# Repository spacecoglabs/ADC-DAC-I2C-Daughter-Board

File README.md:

# ADC-DAC-I2C-Daughter-Board
A simple KiCAD design for an I2C based daughter board featuring a DAC and a ADC.

## Overview
This repository contains a simple KiCADv6 design for a I2C daughter board featuring a TI DAC5571 DAC and a TI ADC081C021 ADC. This design allows for simultaneous electrical connections to the DAC and ADC using the same reference ground utilizing the provided three pin screw terminal.

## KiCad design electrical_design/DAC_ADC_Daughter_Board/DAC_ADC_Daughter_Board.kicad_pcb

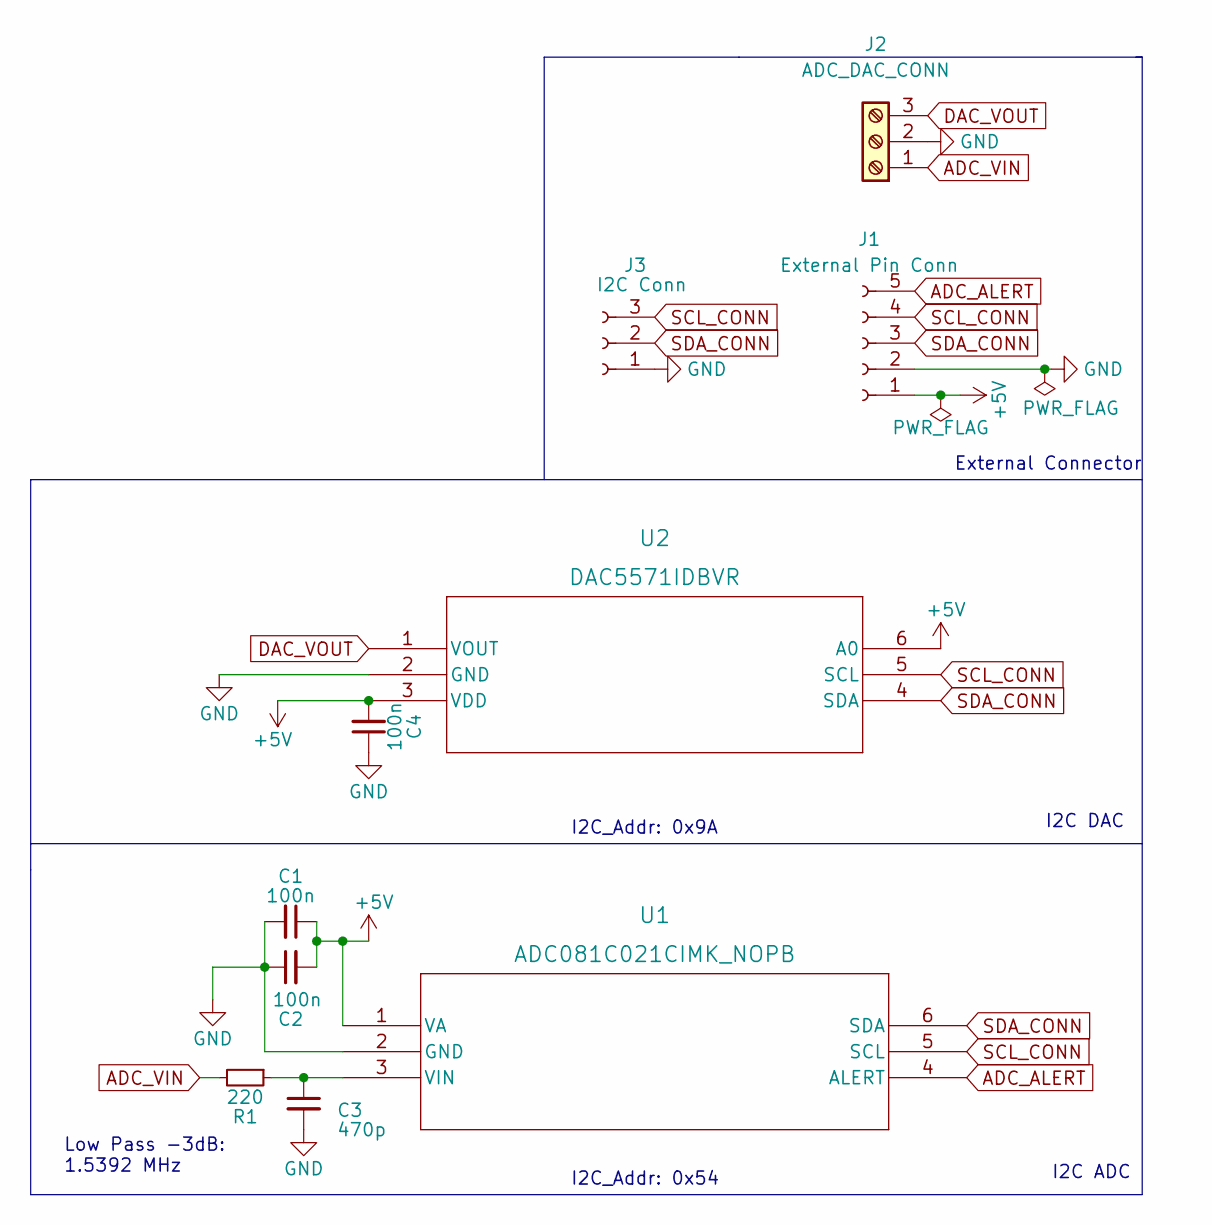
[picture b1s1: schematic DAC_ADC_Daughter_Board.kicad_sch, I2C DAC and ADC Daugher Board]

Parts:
C1, C2, C4: 100n; C_0603_1608Metric; LCSC C14663
C3: 470p; C_0603_1608Metric; LCSC C1620
J1: External Pin Conn; Conn_5
J2: ADC_DAC_CONN; ThreePinScrewTerminal
J3: I2C Conn; Conn_3
R1: 220; R_0805_2012Metric; LCSC C17557
U1: ADC081C021CIMK_NOPB; ADC081C021CIMK; LCSC C181423
U2: DAC5571IDBVR; LCSC C24061

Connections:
+5V: C1.1, C2.2, C4.2, J1.1, U1.1 (VA), U2.3 (VDD), U2.6 (A0)
ADC_ALERT: J1.5, U1.4 (ALERT)
ADC_VIN: J2.1, R1.2
DAC_VOUT: J2.3, U2.1 (VOUT)
GND: C1.2, C2.1, C3.2, C4.1, J1.2, J2.2, J3.1, U1.2 (GND), U2.2 (GND)
unnamed: C3.1, R1.1, U1.3 (VIN)
SCL_CONN: J1.4, J3.3, U1.5 (SCL), U2.5 (SCL)
SDA_CONN: J1.3, J3.2, U1.6 (SDA), U2.4 (SDA)

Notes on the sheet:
I2C DAC
I2C ADC
External Connector
I2C_Addr: 0x54
Low Pass -3dB: 1.5392 MHz
I2C_Addr: 0x9A

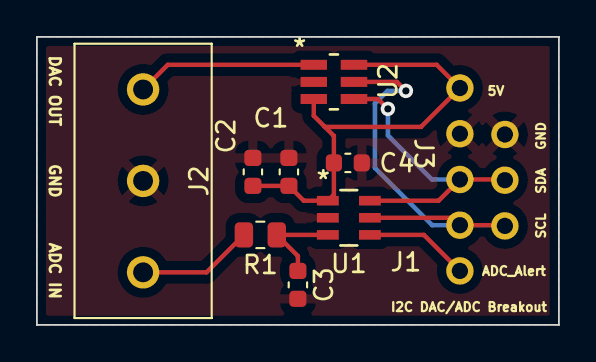
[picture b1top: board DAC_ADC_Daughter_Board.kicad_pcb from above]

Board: 2 copper layers, 29.0 x 16.0 mm, 10 parts (0 on the bottom side), 8 nets.

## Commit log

2024-03-03 initial commit of design
2024-03-03 update documentation
2024-03-03 resize images
2024-03-03 change i2c address of DAC
